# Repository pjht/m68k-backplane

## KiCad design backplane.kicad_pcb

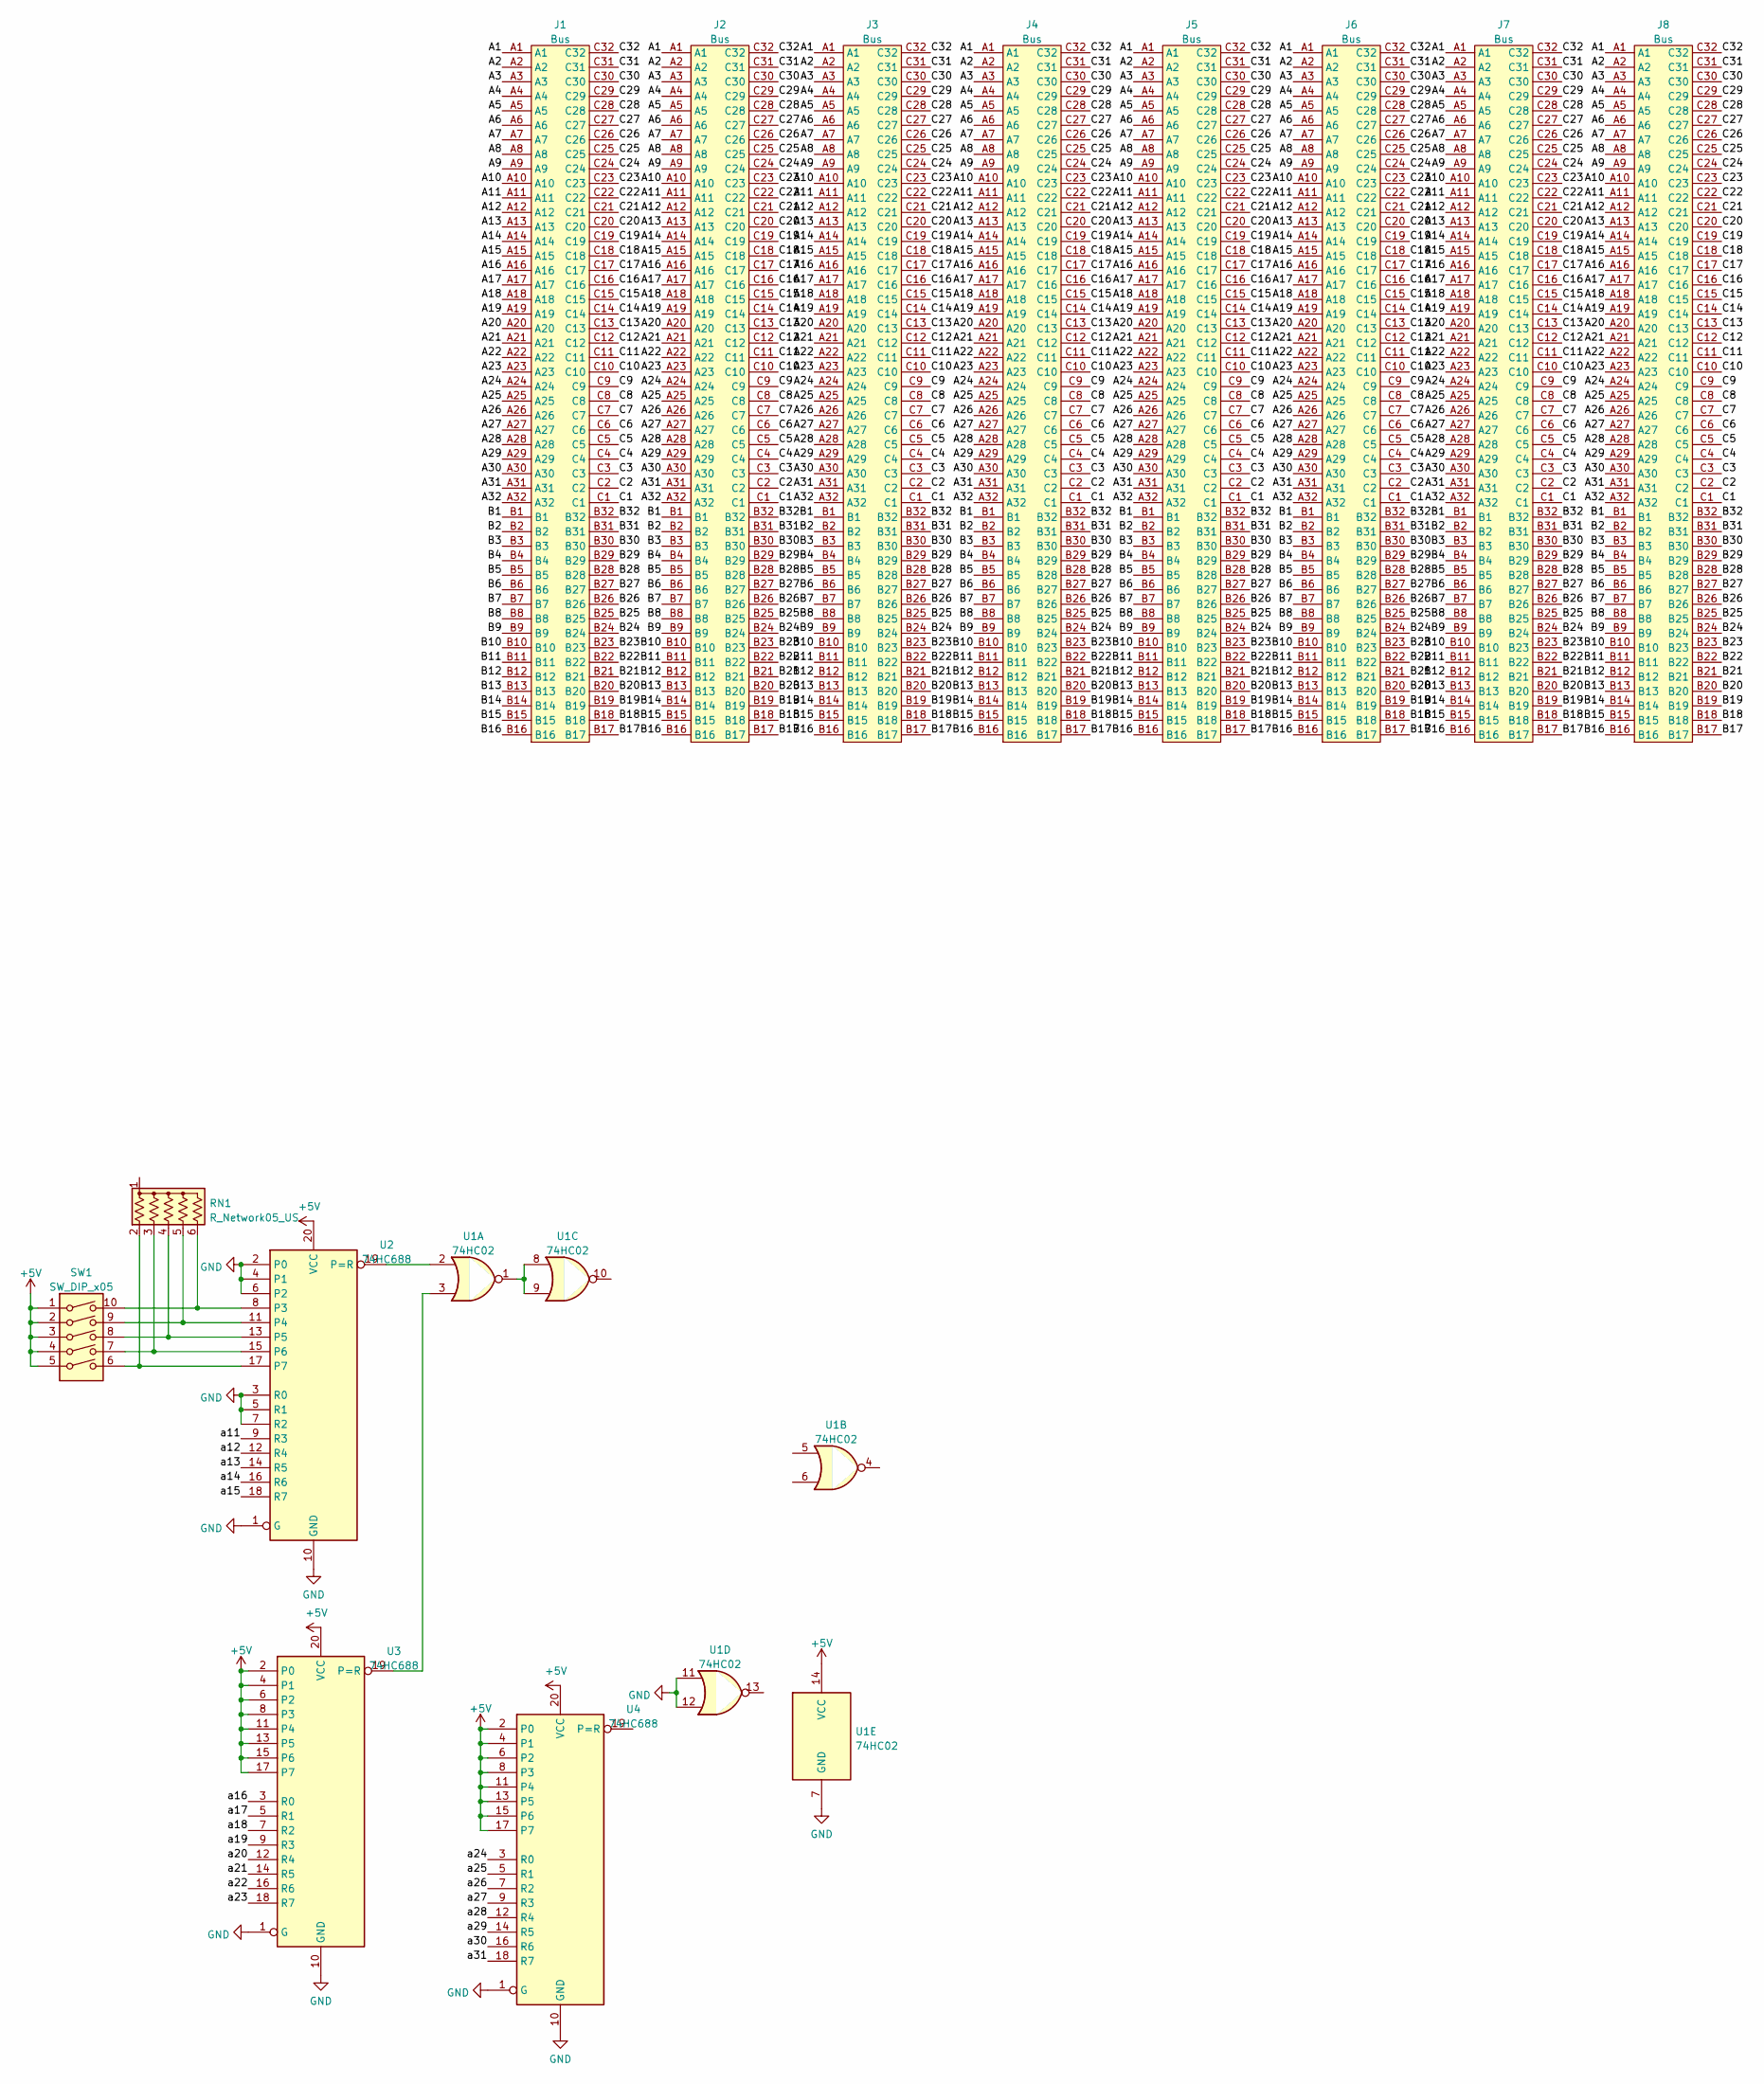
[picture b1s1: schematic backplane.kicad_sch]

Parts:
J1, J2, J3, J4, J5, J6, J7, J8: Bus; TE_535043-4
RN1: R_Network05_US; R_Array_SIP6
SW1: SW_DIP_x05; DIP-10_W7.62mm
U1: 74HC02; SOIC-14W_7.5x9mm_P1.27mm
U2, U3, U4: 74HC688; SOIC-20W_7.5x12.8mm_P1.27mm

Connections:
+5V: SW1.1, SW1.2, SW1.3, SW1.4, SW1.5, U1.14 (VCC), U2.20 (VCC), U3.2 (P0), U3.4 (P1), U3.6 (P2), U3.8 (P3), U3.11 (P4), U3.13 (P5), U3.15 (P6), U3.17 (P7), U3.20 (VCC), U4.2 (P0), U4.4 (P1), U4.6 (P2), U4.8 (P3), U4.11 (P4), U4.13 (P5), U4.15 (P6), U4.17 (P7), U4.20 (VCC)
/A1: J1.A1, J2.A1, J3.A1, J4.A1, J5.A1, J6.A1, J7.A1, J8.A1
/A2: J1.A2, J2.A2, J3.A2, J4.A2, J5.A2, J6.A2, J7.A2, J8.A2
/A3: J1.A3, J2.A3, J3.A3, J4.A3, J5.A3, J6.A3, J7.A3, J8.A3
/A4: J1.A4, J2.A4, J3.A4, J4.A4, J5.A4, J6.A4, J7.A4, J8.A4
/A5: J1.A5, J2.A5, J3.A5, J4.A5, J5.A5, J6.A5, J7.A5, J8.A5
/A6: J1.A6, J2.A6, J3.A6, J4.A6, J5.A6, J6.A6, J7.A6, J8.A6
/A7: J1.A7, J2.A7, J3.A7, J4.A7, J5.A7, J6.A7, J7.A7, J8.A7
/A8: J1.A8, J2.A8, J3.A8, J4.A8, J5.A8, J6.A8, J7.A8, J8.A8
/A9: J1.A9, J2.A9, J3.A9, J4.A9, J5.A9, J6.A9, J7.A9, J8.A9
/A10: J1.A10, J2.A10, J3.A10, J4.A10, J5.A10, J6.A10, J7.A10, J8.A10
/A11: J1.A11, J2.A11, J3.A11, J4.A11, J5.A11, J6.A11, J7.A11, J8.A11
/A12: J1.A12, J2.A12, J3.A12, J4.A12, J5.A12, J6.A12, J7.A12, J8.A12
/A13: J1.A13, J2.A13, J3.A13, J4.A13, J5.A13, J6.A13, J7.A13, J8.A13
/A14: J1.A14, J2.A14, J3.A14, J4.A14, J5.A14, J6.A14, J7.A14, J8.A14
/A15: J1.A15, J2.A15, J3.A15, J4.A15, J5.A15, J6.A15, J7.A15, J8.A15
/A16: J1.A16, J2.A16, J3.A16, J4.A16, J5.A16, J6.A16, J7.A16, J8.A16
/A17: J1.A17, J2.A17, J3.A17, J4.A17, J5.A17, J6.A17, J7.A17, J8.A17
/A18: J1.A18, J2.A18, J3.A18, J4.A18, J5.A18, J6.A18, J7.A18, J8.A18
/A19: J1.A19, J2.A19, J3.A19, J4.A19, J5.A19, J6.A19, J7.A19, J8.A19
/A20: J1.A20, J2.A20, J3.A20, J4.A20, J5.A20, J6.A20, J7.A20, J8.A20
/A21: J1.A21, J2.A21, J3.A21, J4.A21, J5.A21, J6.A21, J7.A21, J8.A21
/A22: J1.A22, J2.A22, J3.A22, J4.A22, J5.A22, J6.A22, J7.A22, J8.A22
/A23: J1.A23, J2.A23, J3.A23, J4.A23, J5.A23, J6.A23, J7.A23, J8.A23
/A24: J1.A24, J2.A24, J3.A24, J4.A24, J5.A24, J6.A24, J7.A24, J8.A24
/A25: J1.A25, J2.A25, J3.A25, J4.A25, J5.A25, J6.A25, J7.A25, J8.A25
/A26: J1.A26, J2.A26, J3.A26, J4.A26, J5.A26, J6.A26, J7.A26, J8.A26
/A27: J1.A27, J2.A27, J3.A27, J4.A27, J5.A27, J6.A27, J7.A27, J8.A27
/A28: J1.A28, J2.A28, J3.A28, J4.A28, J5.A28, J6.A28, J7.A28, J8.A28
/A29: J1.A29, J2.A29, J3.A29, J4.A29, J5.A29, J6.A29, J7.A29, J8.A29
/A30: J1.A30, J2.A30, J3.A30, J4.A30, J5.A30, J6.A30, J7.A30, J8.A30
/A31: J1.A31, J2.A31, J3.A31, J4.A31, J5.A31, J6.A31, J7.A31, J8.A31
/A32: J1.A32, J2.A32, J3.A32, J4.A32, J5.A32, J6.A32, J7.A32, J8.A32
/B1: J1.B1, J2.B1, J3.B1, J4.B1, J5.B1, J6.B1, J7.B1, J8.B1
/B2: J1.B2, J2.B2, J3.B2, J4.B2, J5.B2, J6.B2, J7.B2, J8.B2
/B3: J1.B3, J2.B3, J3.B3, J4.B3, J5.B3, J6.B3, J7.B3, J8.B3
/B4: J1.B4, J2.B4, J3.B4, J4.B4, J5.B4, J6.B4, J7.B4, J8.B4
/B5: J1.B5, J2.B5, J3.B5, J4.B5, J5.B5, J6.B5, J7.B5, J8.B5
/B6: J1.B6, J2.B6, J3.B6, J4.B6, J5.B6, J6.B6, J7.B6, J8.B6
/B7: J1.B7, J2.B7, J3.B7, J4.B7, J5.B7, J6.B7, J7.B7, J8.B7
/B8: J1.B8, J2.B8, J3.B8, J4.B8, J5.B8, J6.B8, J7.B8, J8.B8
/B9: J1.B9, J2.B9, J3.B9, J4.B9, J5.B9, J6.B9, J7.B9, J8.B9
/B10: J1.B10, J2.B10, J3.B10, J4.B10, J5.B10, J6.B10, J7.B10, J8.B10
/B11: J1.B11, J2.B11, J3.B11, J4.B11, J5.B11, J6.B11, J7.B11, J8.B11
/B12: J1.B12, J2.B12, J3.B12, J4.B12, J5.B12, J6.B12, J7.B12, J8.B12
/B13: J1.B13, J2.B13, J3.B13, J4.B13, J5.B13, J6.B13, J7.B13, J8.B13
/B14: J1.B14, J2.B14, J3.B14, J4.B14, J5.B14, J6.B14, J7.B14, J8.B14
/B15: J1.B15, J2.B15, J3.B15, J4.B15, J5.B15, J6.B15, J7.B15, J8.B15
/B16: J1.B16, J2.B16, J3.B16, J4.B16, J5.B16, J6.B16, J7.B16, J8.B16
/B17: J1.B17, J2.B17, J3.B17, J4.B17, J5.B17, J6.B17, J7.B17, J8.B17
/B18: J1.B18, J2.B18, J3.B18, J4.B18, J5.B18, J6.B18, J7.B18, J8.B18
/B19: J1.B19, J2.B19, J3.B19, J4.B19, J5.B19, J6.B19, J7.B19, J8.B19
/B20: J1.B20, J2.B20, J3.B20, J4.B20, J5.B20, J6.B20, J7.B20, J8.B20
/B21: J1.B21, J2.B21, J3.B21, J4.B21, J5.B21, J6.B21, J7.B21, J8.B21
/B22: J1.B22, J2.B22, J3.B22, J4.B22, J5.B22, J6.B22, J7.B22, J8.B22
/B23: J1.B23, J2.B23, J3.B23, J4.B23, J5.B23, J6.B23, J7.B23, J8.B23
/B24: J1.B24, J2.B24, J3.B24, J4.B24, J5.B24, J6.B24, J7.B24, J8.B24
/B25: J1.B25, J2.B25, J3.B25, J4.B25, J5.B25, J6.B25, J7.B25, J8.B25
/B26: J1.B26, J2.B26, J3.B26, J4.B26, J5.B26, J6.B26, J7.B26, J8.B26
/B27: J1.B27, J2.B27, J3.B27, J4.B27, J5.B27, J6.B27, J7.B27, J8.B27
/B28: J1.B28, J2.B28, J3.B28, J4.B28, J5.B28, J6.B28, J7.B28, J8.B28
/B29: J1.B29, J2.B29, J3.B29, J4.B29, J5.B29, J6.B29, J7.B29, J8.B29
/B30: J1.B30, J2.B30, J3.B30, J4.B30, J5.B30, J6.B30, J7.B30, J8.B30
/B31: J1.B31, J2.B31, J3.B31, J4.B31, J5.B31, J6.B31, J7.B31, J8.B31
/B32: J1.B32, J2.B32, J3.B32, J4.B32, J5.B32, J6.B32, J7.B32, J8.B32
/C1: J1.C1, J2.C1, J3.C1, J4.C1, J5.C1, J6.C1, J7.C1, J8.C1
/C2: J1.C2, J2.C2, J3.C2, J4.C2, J5.C2, J6.C2, J7.C2, J8.C2
/C3: J1.C3, J2.C3, J3.C3, J4.C3, J5.C3, J6.C3, J7.C3, J8.C3
/C4: J1.C4, J2.C4, J3.C4, J4.C4, J5.C4, J6.C4, J7.C4, J8.C4
/C5: J1.C5, J2.C5, J3.C5, J4.C5, J5.C5, J6.C5, J7.C5, J8.C5
/C6: J1.C6, J2.C6, J3.C6, J4.C6, J5.C6, J6.C6, J7.C6, J8.C6
/C7: J1.C7, J2.C7, J3.C7, J4.C7, J5.C7, J6.C7, J7.C7, J8.C7
/C8: J1.C8, J2.C8, J3.C8, J4.C8, J5.C8, J6.C8, J7.C8, J8.C8
/C9: J1.C9, J2.C9, J3.C9, J4.C9, J5.C9, J6.C9, J7.C9, J8.C9
/C10: J1.C10, J2.C10, J3.C10, J4.C10, J5.C10, J6.C10, J7.C10, J8.C10
/C11: J1.C11, J2.C11, J3.C11, J4.C11, J5.C11, J6.C11, J7.C11, J8.C11
/C12: J1.C12, J2.C12, J3.C12, J4.C12, J5.C12, J6.C12, J7.C12, J8.C12
/C13: J1.C13, J2.C13, J3.C13, J4.C13, J5.C13, J6.C13, J7.C13, J8.C13
/C14: J1.C14, J2.C14, J3.C14, J4.C14, J5.C14, J6.C14, J7.C14, J8.C14
/C15: J1.C15, J2.C15, J3.C15, J4.C15, J5.C15, J6.C15, J7.C15, J8.C15
/C16: J1.C16, J2.C16, J3.C16, J4.C16, J5.C16, J6.C16, J7.C16, J8.C16
/C17: J1.C17, J2.C17, J3.C17, J4.C17, J5.C17, J6.C17, J7.C17, J8.C17
/C18: J1.C18, J2.C18, J3.C18, J4.C18, J5.C18, J6.C18, J7.C18, J8.C18
/C19: J1.C19, J2.C19, J3.C19, J4.C19, J5.C19, J6.C19, J7.C19, J8.C19
/C20: J1.C20, J2.C20, J3.C20, J4.C20, J5.C20, J6.C20, J7.C20, J8.C20
/C21: J1.C21, J2.C21, J3.C21, J4.C21, J5.C21, J6.C21, J7.C21, J8.C21
/C22: J1.C22, J2.C22, J3.C22, J4.C22, J5.C22, J6.C22, J7.C22, J8.C22
/C23: J1.C23, J2.C23, J3.C23, J4.C23, J5.C23, J6.C23, J7.C23, J8.C23
/C24: J1.C24, J2.C24, J3.C24, J4.C24, J5.C24, J6.C24, J7.C24, J8.C24
/C25: J1.C25, J2.C25, J3.C25, J4.C25, J5.C25, J6.C25, J7.C25, J8.C25
/C26: J1.C26, J2.C26, J3.C26, J4.C26, J5.C26, J6.C26, J7.C26, J8.C26
/C27: J1.C27, J2.C27, J3.C27, J4.C27, J5.C27, J6.C27, J7.C27, J8.C27
/C28: J1.C28, J2.C28, J3.C28, J4.C28, J5.C28, J6.C28, J7.C28, J8.C28
/C29: J1.C29, J2.C29, J3.C29, J4.C29, J5.C29, J6.C29, J7.C29, J8.C29
/C30: J1.C30, J2.C30, J3.C30, J4.C30, J5.C30, J6.C30, J7.C30, J8.C30
/C31: J1.C31, J2.C31, J3.C31, J4.C31, J5.C31, J6.C31, J7.C31, J8.C31
/C32: J1.C32, J2.C32, J3.C32, J4.C32, J5.C32, J6.C32, J7.C32, J8.C32
/a11: U2.9 (R3)
/a12: U2.12 (R4)
/a13: U2.14 (R5)
/a14: U2.16 (R6)
/a15: U2.18 (R7)
/a16: U3.3 (R0)
/a17: U3.5 (R1)
/a18: U3.7 (R2)
/a19: U3.9 (R3)
/a20: U3.12 (R4)
/a21: U3.14 (R5)
/a22: U3.16 (R6)
/a23: U3.18 (R7)
/a24: U4.3 (R0)
/a25: U4.5 (R1)
/a26: U4.7 (R2)
/a27: U4.9 (R3)
/a28: U4.12 (R4)
/a29: U4.14 (R5)
/a30: U4.16 (R6)
/a31: U4.18 (R7)
GND: U1.7 (GND), U1.11, U1.12, U2.1 (G), U2.2 (P0), U2.3 (R0), U2.4 (P1), U2.5 (R1), U2.6 (P2), U2.7 (R2), U2.10 (GND), U3.1 (G), U3.10 (GND), U4.1 (G), U4.10 (GND)
unnamed: RN1.2 (R1), SW1.6, U2.17 (P7)
unnamed: RN1.3 (R2), SW1.7, U2.15 (P6)
unnamed: RN1.4 (R3), SW1.8, U2.13 (P5)
unnamed: RN1.5 (R4), SW1.9, U2.11 (P4)
unnamed: RN1.6 (R5), SW1.10, U2.8 (P3)
unnamed: U1.1, U1.8, U1.9
unnamed: U1.2, U2.19 (P=R)
unnamed: U1.3, U3.19 (P=R)

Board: 2 copper layers, 14 parts (0 on the bottom side), 106 nets, no tracks yet.
